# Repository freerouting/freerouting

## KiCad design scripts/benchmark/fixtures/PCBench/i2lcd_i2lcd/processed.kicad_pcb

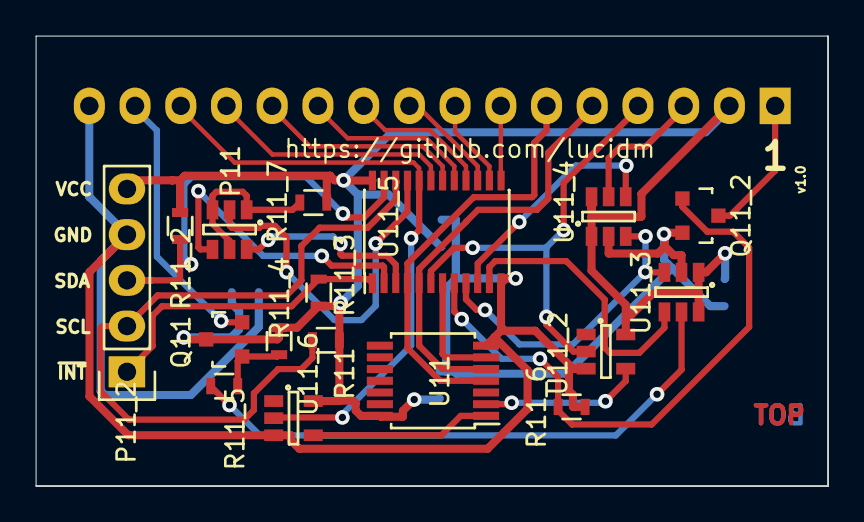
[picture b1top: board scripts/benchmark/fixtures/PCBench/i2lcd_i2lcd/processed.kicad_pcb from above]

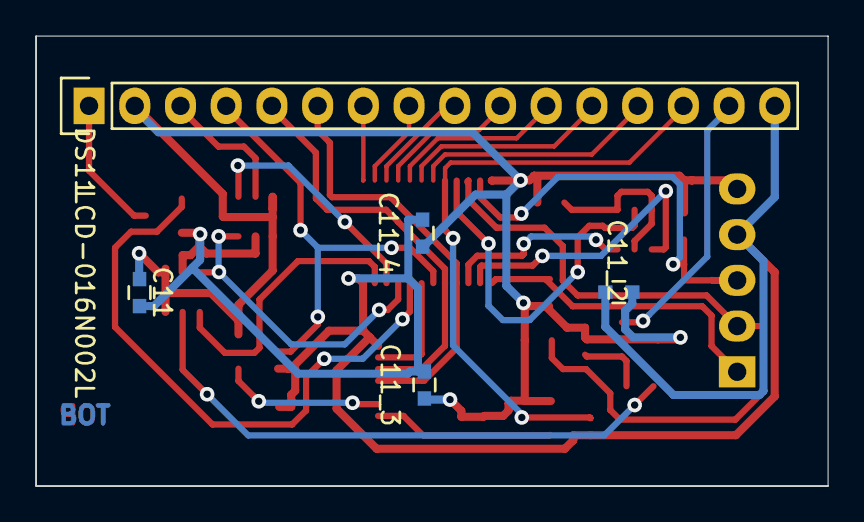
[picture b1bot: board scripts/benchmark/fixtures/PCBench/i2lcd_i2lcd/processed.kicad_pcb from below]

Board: 2 copper layers, 44.0 x 25.0 mm, 22 parts (5 on the bottom side), 32 nets.

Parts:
C11, C11_2, C11_3, C11_4: 100n; C_0603
DS11: LCD-016N002L; Pin_Header_Straight_1x16
P11: CONN_02X03; SOT-23-6
P11_2: CONN_01X05; Pin_Header_Straight_1x05
Q11: BT2N2222; SOT-23
Q11_2: IRLML6244; SOT-23
R11, R11_2, R11_3, R11_5: 4.7k; R_0603
R11_4: 220k; R_0603
R11_6: 100k; R_0603
R11_7: 47k; R_0603
U11: 74LS21; TSSOP-14_4.4x5mm_Pitch0.65mm
U11_2, U11_6: 74AHC1G14; SOT-23-5
U11_3, U11_4: MCP4013T-503; SOT-23-6
U11_5: PCA9535; TSSOP-24_4.4x7.8mm_Pitch0.65mm

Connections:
/D0: DS11.7, U11_5.13
/D1: DS11.8, U11_5.14
/D2: DS11.9, U11_5.15
/D3: DS11.10, U11_5.16
/D4: DS11.11, U11_5.17
/D5: DS11.12, U11_5.18
/D6: DS11.13, U11_5.19
A0: P11.2, U11_5.21
A1: P11.4, U11_5.2
A2: P11.6, U11_5.3
BRHT: R11_5.2, U11_3.5
D7: DS11.14, U11_5.20, U11_6.2
E: DS11.6, U11.4, U11_5.4
IRS: U11.6, U11_5.7
LED+: DS11.15, Q11.2
unnamed: DS11.1, Q11_2.3
unnamed: P11.1, P11.3, P11.5, R11_7.2
unnamed: Q11.1, R11_4.1, R11_5.1
unnamed: U11.2, U11_2.4
unnamed: U11.1, U11_6.4
PWR: Q11_2.1, R11_6.1, U11_5.8
R/~S: DS11.4, U11_2.2, U11_5.6
R/~W: DS11.5, U11.5, U11_5.5
SCL: P11_2.2, R11.1, U11_5.22
SDA: P11_2.3, R11_2.1, U11_5.23
U/~D: U11_3.3, U11_4.3, U11_5.9
VCC: C11.1, C11_2.1, C11_3.1, C11_4.1, DS11.2, P11_2.5, Q11.3, R11.2, R11_2.2, R11_3.1, R11_4.2, R11_7.1, U11.14, U11_2.5, U11_3.1, U11_3.6, U11_4.1, U11_4.6, U11_5.24, U11_6.5
VO: DS11.3, U11_4.5
Vss: C11.2, C11_2.2, C11_3.2, C11_4.2, DS11.16, P11_2.4, Q11_2.2, R11_6.2, U11.7, U11_2.3, U11_3.2, U11_4.2, U11_5.12, U11_6.3
~ACS: U11_4.4, U11_5.10
~BCS: U11_3.4, U11_5.11
~INT: P11_2.1, R11_3.2, U11_5.1

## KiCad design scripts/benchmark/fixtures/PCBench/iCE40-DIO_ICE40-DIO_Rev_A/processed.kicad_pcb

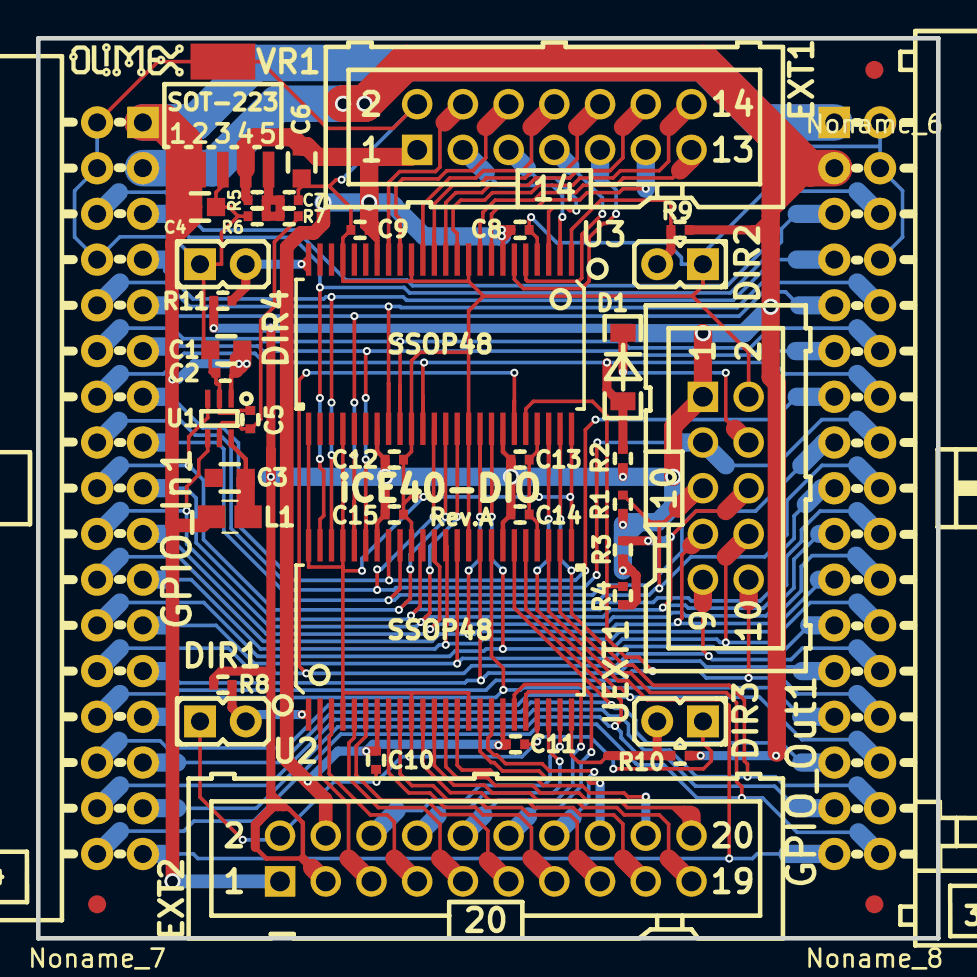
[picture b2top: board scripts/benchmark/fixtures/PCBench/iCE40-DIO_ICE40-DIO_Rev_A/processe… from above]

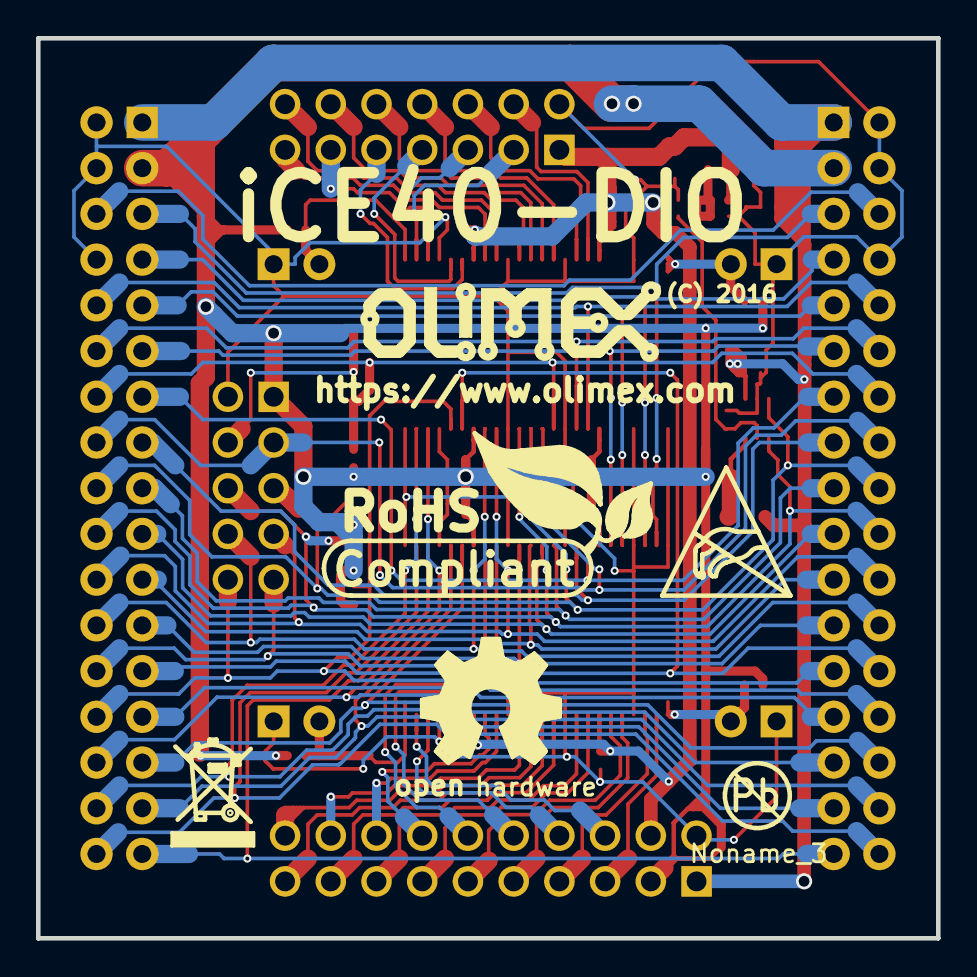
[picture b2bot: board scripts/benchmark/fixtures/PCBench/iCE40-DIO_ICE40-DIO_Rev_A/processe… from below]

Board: 2 copper layers, 50.0 x 50.0 mm, 51 parts (6 on the bottom side), 69 nets.

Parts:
C1, C3, C4, C6: 22uF/6.3V/0603; C_0603_5MIL_DWS
C2, C5, C8, C9, C10, C11, C12, C13, C14, C15: 100nF; C_0402_5MIL_DWS
C7: NA(100nF); C_0402_5MIL_DWS
D1: 1N5819(S4SOD-123); SOD-123_1C-2A_KA
DIR1, DIR2, DIR3, DIR4: HN1x2(Opened); HN1x2
EXT1: BH14S
EXT2: BH20S
GPIO_In1: IDC34R; IDC34R_PCB
GPIO_Out1: BH34R
L1: FB0805/600R/2A; L_0805_5MIL_DWS
Noname_1: OLIMEX_LOGO_TB
Noname_2: LOGO_RECYCLEBIN_1
Noname_3: LOGO_PBFREE
Noname_4: LOGO_OPENHARDWARE_8x8
Noname_5: LOGO_OLIMEX_80
Noname_6, Noname_7, Noname_8: Fiducial1x3
R1, R3: 2.2k; R_0402_5MIL_DWS
R2, R4, R8, R9, R10, R11: 10k; R_0402_5MIL_DWS
R5, R7: 100k/1%; R_0402_5MIL_DWS
R6: 10k/1%; R_0402_5MIL_DWS
Ref**: Val**; LOGO_ROHS_1
Ref**_2: Val**; LOGO_ANTISTATIC_1
U1: MCP47A1T-A0E/LT(SC70-6); SC70-6_Pitch-0.65_2.00x2.10x1.00mm
U2, U3: 74ALVC164245DL(SSOP48); SSOP48_Pitch-0.635_16.00x10.40x2.80mm
UEXT1: BH10S
VR1: MCP1825-ADJE/DC(SOT-223-5); SOT-223-5_Pitch-1.27_6.50x7.00x1.80

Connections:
+3V3: C12.2, C13.2, C14.2, C15.2, EXT2.3, GPIO_In1.3, GPIO_Out1.3, R1.1, R2.1, R3.1, R4.1, R8.1, R9.1, R10.1, R11.1, U2.31, U2.42, U3.31, U3.42, UEXT1.1
+5V: C1.2, C2.2, C4.2, EXT2.1, GPIO_In1.1, GPIO_Out1.1, L1.2, U1.1, VR1.1, VR1.2
/EXTCLK: GPIO_In1.6, GPIO_Out1.6
/GPIO_Pin<5>: GPIO_In1.5, GPIO_Out1.5, U2.47
/GPIO_Pin<7>: GPIO_In1.7, GPIO_Out1.7, U2.46
/GPIO_Pin<9>: GPIO_In1.9, GPIO_Out1.9, U2.44
/GPIO_Pin<10>: GPIO_In1.10, GPIO_Out1.10, U3.32
/GPIO_Pin<11>: GPIO_In1.11, GPIO_Out1.11, U2.43
/GPIO_Pin<12>: GPIO_In1.12, GPIO_Out1.12, U3.33
/GPIO_Pin<13>: GPIO_In1.13, GPIO_Out1.13, U2.41
/GPIO_Pin<15>: GPIO_In1.15, GPIO_Out1.15, U2.40
/GPIO_Pin<17>: GPIO_In1.17, GPIO_Out1.17, U2.38
/GPIO_Pin<19>: GPIO_In1.19, GPIO_Out1.19, U2.37
/GPIO_Pin<21>: GPIO_In1.21, GPIO_Out1.21, U2.36
/GPIO_Pin<23>: GPIO_In1.23, GPIO_Out1.23, U2.35
/GPIO_Pin<25>: GPIO_In1.25, GPIO_Out1.25, U2.33
/GPIO_Pin<27>: GPIO_In1.27, GPIO_Out1.27, U2.32
/GPIO_Pin<29>: GPIO_In1.29, GPIO_Out1.29, U2.30
/GPIO_Pin<30>: GPIO_In1.30, GPIO_Out1.30, U3.46
/GPIO_Pin<31>: GPIO_In1.31, GPIO_Out1.31, U2.29
/GPIO_Pin<32>: GPIO_In1.32, GPIO_Out1.32, U3.47
/GPIO_Pin<33>: GPIO_In1.33, GPIO_Out1.33, U2.27
/GPIO_Pin<34>: GPIO_In1.34, GPIO_Out1.34, U2.26
/IO00: EXT2.5, U2.2
/IO01: EXT2.7, U2.3
/IO02: EXT2.9, U2.5
/IO03: EXT2.11, U2.6
/IO04: EXT2.13, U2.8
/IO05: EXT2.15, U2.9
/IO06: EXT2.17, U2.11
/IO07: EXT2.19, U2.12
/IO08: EXT2.20, U2.13
/IO09: EXT2.18, U2.14
/IO10: EXT2.16, U2.16
/IO11: EXT2.14, U2.17
/IO12: EXT2.12, U2.19
/IO13: EXT2.10, U2.20
/IO14: EXT2.8, U2.22
/IO15: EXT2.6, U2.23
/IO16: EXT1.3, U3.2
/IO17: EXT1.5, U3.3
/IO18: EXT1.7, U3.5
/IO19: EXT1.9, U3.6
/IO20: EXT1.11, U3.8
/IO21: EXT1.13, U3.9
/IO22: EXT1.14, U3.11
/IO23: EXT1.12, U3.12
/IO24: EXT1.10, U3.13
/IO25: EXT1.8, U3.14
/IO26: EXT1.6, U3.16
/IO27: EXT1.4, U3.17
/UEXT_#SS: GPIO_In1.28, GPIO_Out1.28, R4.2, U3.44, UEXT1.10
/UEXT_MISO: GPIO_In1.22, GPIO_Out1.22, U3.40, UEXT1.7
/UEXT_MOSI: GPIO_In1.24, GPIO_Out1.24, U3.41, UEXT1.8
/UEXT_RxD: D1.2, GPIO_In1.14, GPIO_Out1.14, R2.2, U3.35
/UEXT_SCK: GPIO_In1.26, GPIO_Out1.26, U3.43, UEXT1.9
/UEXT_SCL: GPIO_In1.18, GPIO_Out1.18, R1.2, U1.3, U3.37, UEXT1.5
/UEXT_SDA: GPIO_In1.20, GPIO_Out1.20, R3.2, U1.4, U3.38, UEXT1.6
/UEXT_TxD: GPIO_In1.16, GPIO_Out1.16, U3.36, UEXT1.3
/Vdac: C5.2, R7.2, U1.5
GND: C1.1, C2.1, C4.1, C5.1, C6.1, C7.1, C8.1, C9.1, C10.1, C11.1, C12.1, C13.1, C14.1, C15.1, DIR1.1, DIR2.1, DIR3.1, DIR4.1, EXT1.2, EXT2.2, GPIO_In1.2, GPIO_In1.4, GPIO_In1.8, GPIO_Out1.2, GPIO_Out1.4, GPIO_Out1.8, R6.1, U1.2, U2.4, U2.10, U2.15, U2.21, U2.25, U2.28, U2.34, U2.39, U2.45, U2.48, U3.4, U3.10, U3.15, U3.21, U3.25, U3.28, U3.34, U3.39, U3.45, U3.48, UEXT1.2, VR1.3, VR1.6
unnamed: C3.2, L1.1, U1.6
unnamed: C7.2, R5.2, R6.2, R7.1, VR1.5
unnamed: D1.1, UEXT1.4
unnamed: DIR1.2, R8.2, U2.1
unnamed: DIR2.2, R9.2, U3.1
unnamed: DIR3.2, R10.2, U2.24
unnamed: DIR4.2, R11.2, U3.24
VDD: C6.2, C8.2, C9.2, C10.2, C11.2, EXT1.1, EXT2.4, R5.1, U2.7, U2.18, U3.7, U3.18, VR1.4

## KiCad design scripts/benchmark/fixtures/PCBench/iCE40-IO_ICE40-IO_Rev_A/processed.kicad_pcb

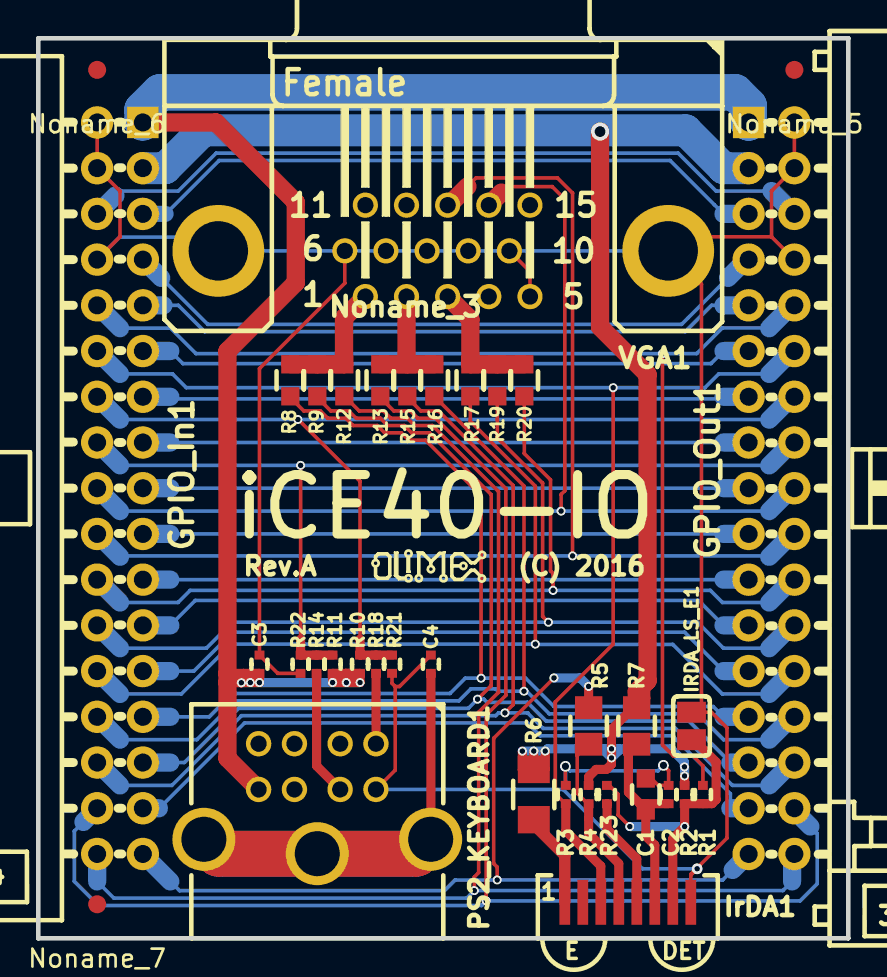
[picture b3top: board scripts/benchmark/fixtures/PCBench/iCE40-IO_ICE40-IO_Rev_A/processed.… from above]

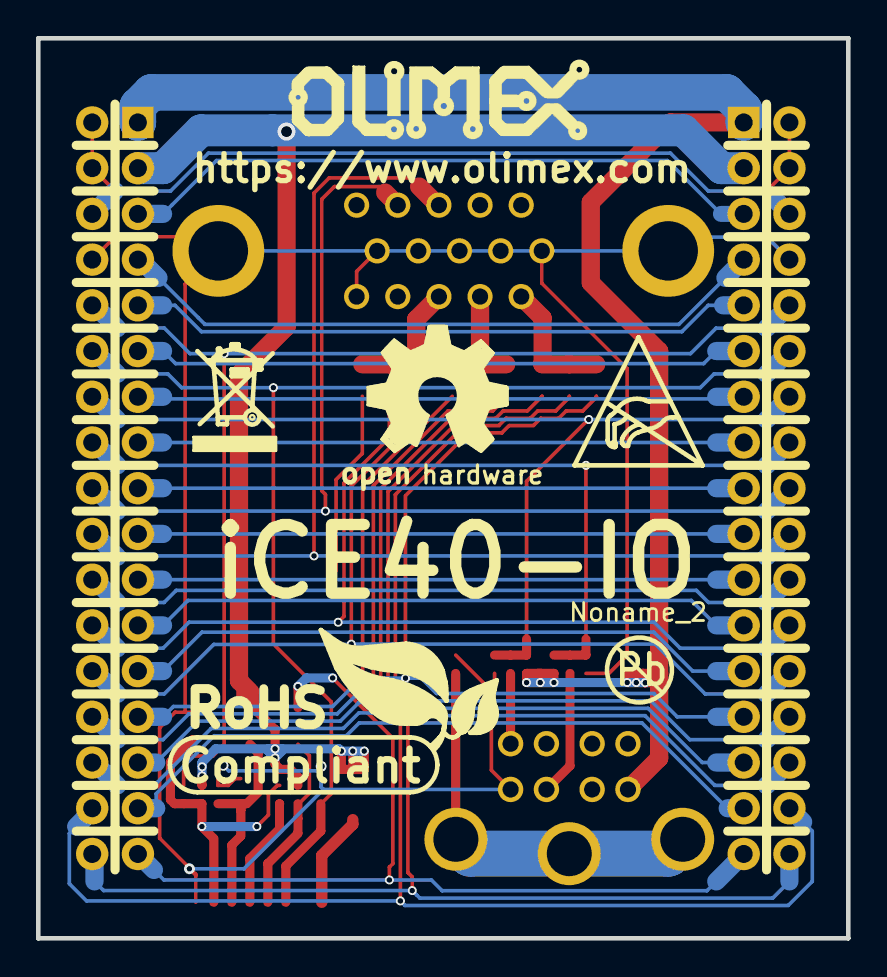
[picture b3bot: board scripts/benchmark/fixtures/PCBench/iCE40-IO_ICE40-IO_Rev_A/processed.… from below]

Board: 2 copper layers, 45.0 x 50.0 mm, 43 parts (6 on the bottom side), 43 nets.

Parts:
C1: 22uF/6.3V; C_0603_5MIL_DWS
C2, C3: 100nF; C_0402_5MIL_DWS
C4: 10nF; C_0402_5MIL_DWS
GPIO_In1: IDC34R; IDC34R_PCB
GPIO_Out1: BH34R
IRDA_LS_E1: Opened; SJ
IrDA1: TFDU4100; TFDU4100_PACK
Noname_1: LOGO_RECYCLEBIN_1
Noname_2: LOGO_PBFREE
Noname_3: OLIMEX_LOGO_SMALL_TB
Noname_4: OLIMEX_LOGO_TB
Noname_5, Noname_6, Noname_7: Fiducial1x3
Noname_8: LOGO_OPENHARDWARE_8x8
PS2_KEYBOARD1: MDR6_MINI-DIN; PS2_MDR6_MINI-DIN
R1, R4, R23: NA; R_0402_5MIL_DWS
R2, R21, R22: 10k; R_0402_5MIL_DWS
R3: NA(10k); R_0402_5MIL_DWS
R5, R7: 47R; R_0805_5MIL_DWS
R6: 15R; R_1206_5MIL_DWS
R8, R13, R17: 470R; C_0603_5MIL_DWS
R9, R15, R19: 1k; C_0603_5MIL_DWS
R10, R11: 5.6k; R_0402_5MIL_DWS
R12, R16, R20: 1.8k; C_0603_5MIL_DWS
R14, R18: 200R; R_0402_5MIL_DWS
Ref**: Val**; LOGO_ANTISTATIC_1
Ref**_2: Val**; LOGO_ROHS_1
VGA1: VGA15-F(CD0515S21J0)

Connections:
+3V3: GPIO_In1.3, GPIO_Out1.3, R2.2, R4.2, R6.2, R7.2
+5V: C3.2, GPIO_In1.1, GPIO_Out1.1, PS2_KEYBOARD1.4, R10.1, R11.1
/EXTCLK: GPIO_In1.6, GPIO_Out1.6
/GPIO_Pin<5>: GPIO_In1.5, GPIO_Out1.5
/GPIO_Pin<7>: GPIO_In1.7, GPIO_Out1.7
/GPIO_Pin<9>: GPIO_In1.9, GPIO_Out1.9
/GPIO_Pin<11>: GPIO_In1.11, GPIO_Out1.11
/GPIO_Pin<13>: GPIO_In1.13, GPIO_Out1.13
/GPIO_Pin<15>: GPIO_In1.15, GPIO_Out1.15
/GPIO_Pin<17>: GPIO_In1.17, GPIO_Out1.17
/GPIO_Pin<19>: GPIO_In1.19, GPIO_Out1.19
/GPIO_Pin<21>: GPIO_In1.21, GPIO_Out1.21
/GPIO_Pin<23>: GPIO_In1.23, GPIO_Out1.23
/GPIO_Pin<25>: GPIO_In1.25, GPIO_Out1.25
/GPIO_Pin<31>: GPIO_In1.31, GPIO_Out1.31
/IrDA_Rx: GPIO_In1.12, GPIO_Out1.12, IrDA1.3, R3.1
/IrDA_SC: GPIO_In1.10, GPIO_Out1.10, R1.1
/IrDA_Tx: GPIO_In1.33, GPIO_Out1.33, R5.1
/PS2_CLK: GPIO_In1.14, GPIO_Out1.14, R10.2, R18.1, R21.1
/PS2_DATA: GPIO_In1.16, GPIO_Out1.16, R11.2, R14.1, R22.1
/VGA_BLUE1: GPIO_In1.26, GPIO_Out1.26, R17.1
/VGA_BLUE2: GPIO_In1.24, GPIO_Out1.24, R19.1
/VGA_BLUE3: GPIO_In1.22, GPIO_Out1.22, R20.1
/VGA_GREEN1: GPIO_In1.32, GPIO_Out1.32, R13.1
/VGA_GREEN2: GPIO_In1.30, GPIO_Out1.30, R15.1
/VGA_GREEN3: GPIO_In1.28, GPIO_Out1.28, R16.1
/VGA_HSYNC: GPIO_In1.20, GPIO_Out1.20, VGA1.13
/VGA_RED1: GPIO_In1.27, GPIO_Out1.27, R8.1
/VGA_RED2: GPIO_In1.29, GPIO_Out1.29, R9.1
/VGA_RED3: GPIO_In1.34, GPIO_Out1.34, R12.1
/VGA_VSYNC: GPIO_In1.18, GPIO_Out1.18, VGA1.14
GND: C1.1, C2.1, C3.1, C4.1, GPIO_In1.2, GPIO_In1.4, GPIO_In1.8, GPIO_Out1.2, GPIO_Out1.4, GPIO_Out1.8, IRDA_LS_E1.2, IrDA1.8, PS2_KEYBOARD1.3, R3.2, R21.2, R22.2, VGA1.5, VGA1.6, VGA1.7, VGA1.8, VGA1.9, VGA1.10, VGA1.16, VGA1.17
unnamed: C1.2, C2.2, IrDA1.6, R7.1
unnamed: C4.2, PS2_KEYBOARD1.9
unnamed: IRDA_LS_E1.1, IrDA1.7, R1.2, R2.1, R23.2
unnamed: IrDA1.1, R6.1
unnamed: IrDA1.4, R4.1, R5.2
unnamed: IrDA1.5, R23.1
unnamed: PS2_KEYBOARD1.1, R14.2
unnamed: PS2_KEYBOARD1.5, R18.2
unnamed: R8.2, R9.2, R12.2, VGA1.1
unnamed: R13.2, R15.2, R16.2, VGA1.2
unnamed: R17.2, R19.2, R20.2, VGA1.3

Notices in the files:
scripts/benchmark/fixtures/PCBench/iCE40-DIO_ICE40-DIO_Rev_A/processed.kicad_pcb:
(C) 2016
